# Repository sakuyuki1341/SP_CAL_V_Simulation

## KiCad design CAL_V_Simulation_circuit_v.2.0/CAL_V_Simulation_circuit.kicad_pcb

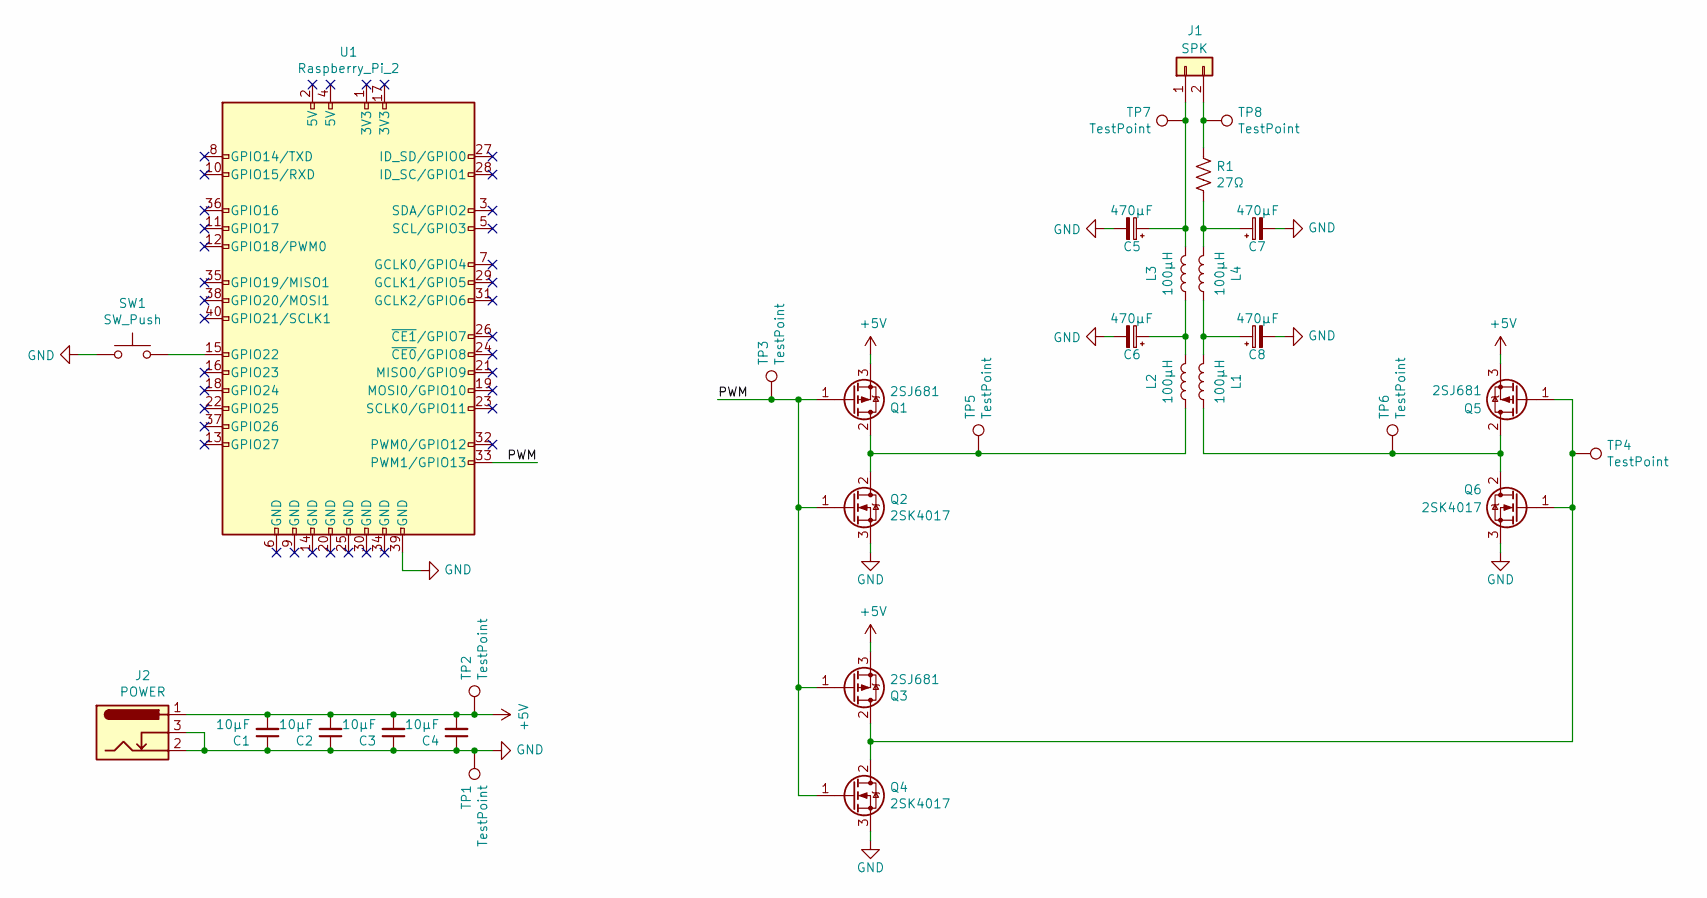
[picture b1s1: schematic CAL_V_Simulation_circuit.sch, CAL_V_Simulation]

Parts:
C1, C2, C3, C4: 10μF; C_Disc_D5.0mm_W2.5mm_P5.00mm
C5, C6, C7, C8: 470μF; CP_Radial_D8.0mm_P5.00mm
J1: SPK; JST_XH_B2B-XH-A_1x02_P2.50mm_Vertical
J2: POWER; BarrelJack_Horizontal
L1, L2, L3, L4: 100μH; L_Radial_D8.7mm_P5.00mm_Fastron_07HCP
Q1, Q3, Q5: 2SJ681
Q2, Q4, Q6: 2SK4017
R1: 27Ω; R_Axial_DIN0309_L9.0mm_D3.2mm_P12.70mm_Horizontal
SW1: SW_Push; SW_PUSH_6mm
TP1, TP2, TP3, TP4, TP5, TP6, TP7, TP8: TestPoint; TestPoint_Loop_D3.50mm_Drill0.9mm_Beaded
U1: Raspberry_Pi_2; PinSocket_2x20_P2.54mm_Vertical

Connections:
+5V: C1.2, C2.2, C3.2, C4.2, J2.1, Q1.3 (S), Q3.3 (S), Q5.3 (S), TP2.1; also elsewhere on the board
/PWM: Q1.1 (G), Q2.1 (G), Q3.1 (G), Q4.1 (G), TP3.1, U1.33 (PWM1/GPIO13); also elsewhere on the board
GND: C1.1, C2.1, C3.1, C4.1, C5.2, C6.2, C7.2, C8.2, J2.2, J2.3, Q2.3 (S), Q4.3 (S), Q6.3 (S), SW1.1, TP1.1, U1.39 (GND); also elsewhere on the board
unnamed: C5.1, J1.1, L3.2, TP7.1
unnamed: C6.1, L2.2, L3.1
unnamed: C7.1, L4.2, R1.2
unnamed: C8.1, L1.2, L4.1
unnamed: J1.2, R1.1, TP8.1
unnamed: L1.1, Q5.2 (D), Q6.2 (D), TP6.1
unnamed: L2.1, Q1.2 (D), Q2.2 (D), TP5.1
unnamed: Q3.2 (D), Q4.2 (D), Q5.1 (G), Q6.1 (G), TP4.1
unnamed: SW1.2, U1.15 (GPIO22)

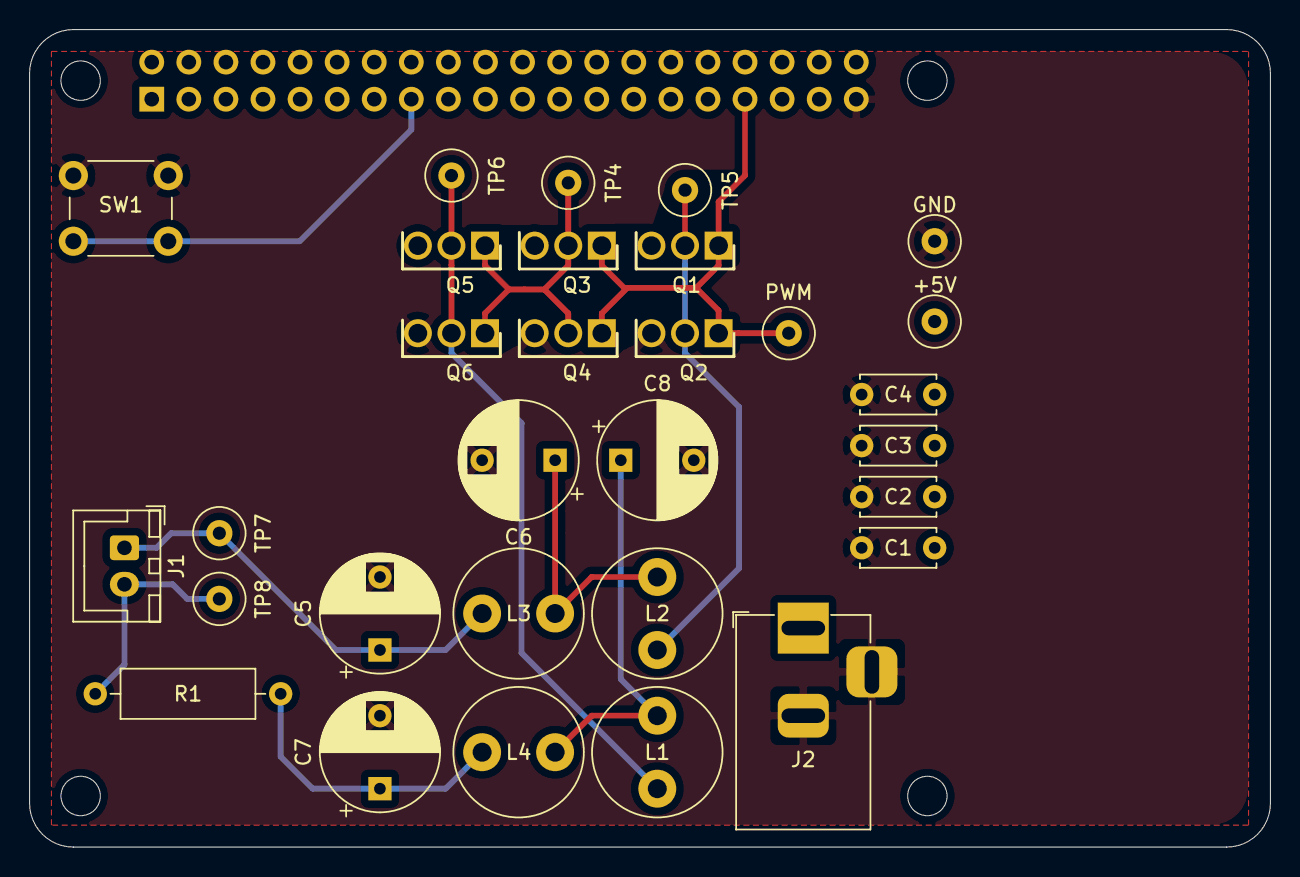
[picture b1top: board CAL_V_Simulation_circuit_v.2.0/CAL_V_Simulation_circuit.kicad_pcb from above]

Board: 2 copper layers, 85.0 x 56.0 mm, 35 parts (1 on the bottom side), 12 nets.

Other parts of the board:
+5V: TestPoint; TestPoint_Loop_D3.50mm_Drill0.9mm_Beaded
GND: TestPoint; TestPoint_Loop_D3.50mm_Drill0.9mm_Beaded
MH1, MH2, MH3, MH4: MountingHole_2.7mm_M2.5
PWM: TestPoint; TestPoint_Loop_D3.50mm_Drill0.9mm_Beaded

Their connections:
+5V: +5V.1; also elsewhere on the board
/PWM: PWM.1; also elsewhere on the board
GND: GND.1; also elsewhere on the board

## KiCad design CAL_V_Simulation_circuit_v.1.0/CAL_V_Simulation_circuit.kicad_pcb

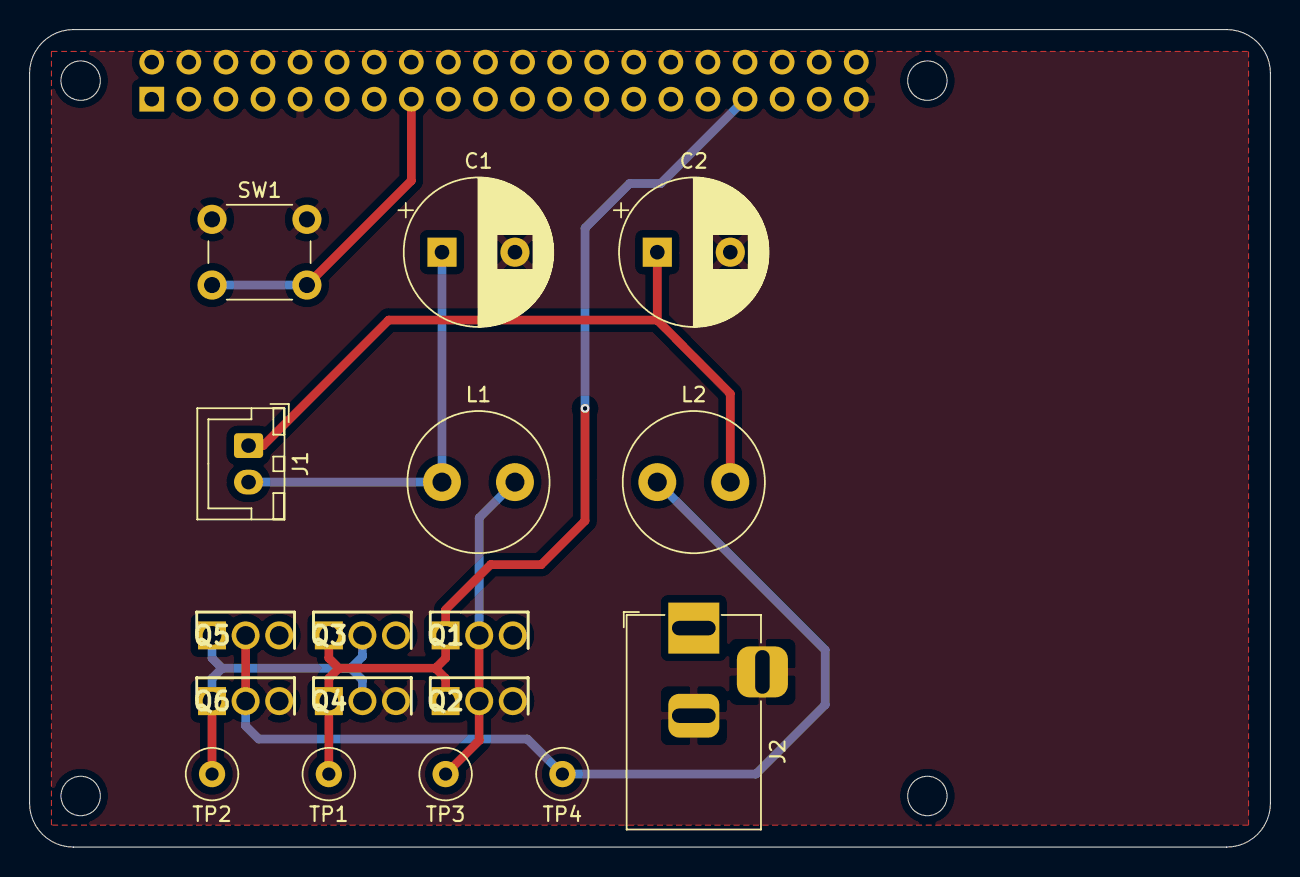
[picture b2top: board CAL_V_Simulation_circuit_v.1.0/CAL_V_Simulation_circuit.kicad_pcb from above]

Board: 2 copper layers, 85.0 x 56.0 mm, 22 parts (1 on the bottom side), 9 nets.

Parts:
C1, C2: 470μF; CP_Radial_D10.0mm_P5.00mm
J1: SPK; JST_XH_B2B-XH-A_1x02_P2.50mm_Vertical
J2: POWER; BarrelJack_Horizontal
L1, L2: 100μH; L_Radial_D9.5mm_P5.00mm_Fastron_07HVP
MH1, MH2, MH3, MH4: MountingHole_2.7mm_M2.5
Q1, Q3, Q5: 2SJ681_Q_; TO230P250X650X900-3P
Q2, Q4, Q6: 2SK4017_Q_; TO230P250X650X900-3P
SW1: SW_Push; SW_PUSH_6mm
TP1, TP2, TP3, TP4: TestPoint; TestPoint_Loop_D3.50mm_Drill0.9mm_Beaded
U1: Raspberry_Pi_2; PinSocket_2x20_P2.54mm_Vertical

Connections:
+5V: J2.1, Q1.3, Q3.3, Q5.3, U1.2, U1.4
/PWM: Q1.1, Q2.1, Q3.1, Q4.1, TP1.1, U1.33
GND: C1.2, C2.2, J2.2, J2.3, Q2.3, Q4.3, Q6.3, SW1.1, U1.9, U1.25, U1.39
unnamed: C1.1, J1.2, L1.2
unnamed: C2.1, J1.1, L2.2
unnamed: L1.1, Q1.2, Q2.2, TP3.1
unnamed: L2.1, Q5.2, Q6.2, TP4.1
unnamed: Q3.2, Q4.2, Q5.1, Q6.1, TP2.1
unnamed: SW1.2, U1.15

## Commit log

2020-07-04 CAL_V_Simulationの共有
2020-07-09 回路図の訂正版を追加
2020-07-11 mainファイルの更新
2020-07-16 main_1ms_busyをmainへ改名。pwm信号の周波数と分解能を別変数として定義。
2020-07-16 自動読み込み、自動実行のためのファイル作成
2020-07-16 自動読み込み、自動再生を実行するプログラム(作成中)
2020-07-16 シミュレーション部を別関数として定義
2020-07-26 time_startの再設定値の変更
2020-07-26 回路のバージョンがわかるように名称を変更
2020-08-08 CAL_V_Simulation_circuit_v.2.0の追加
2020-10-15 ラズパイと同期
2020-10-18 単純な呼吸と、実データから抜粋したもの。二種のテストデータを追加
2020-11-29 一部変更がありました
2021-06-19 回路図とメインプログラムのtxt版アップロード
